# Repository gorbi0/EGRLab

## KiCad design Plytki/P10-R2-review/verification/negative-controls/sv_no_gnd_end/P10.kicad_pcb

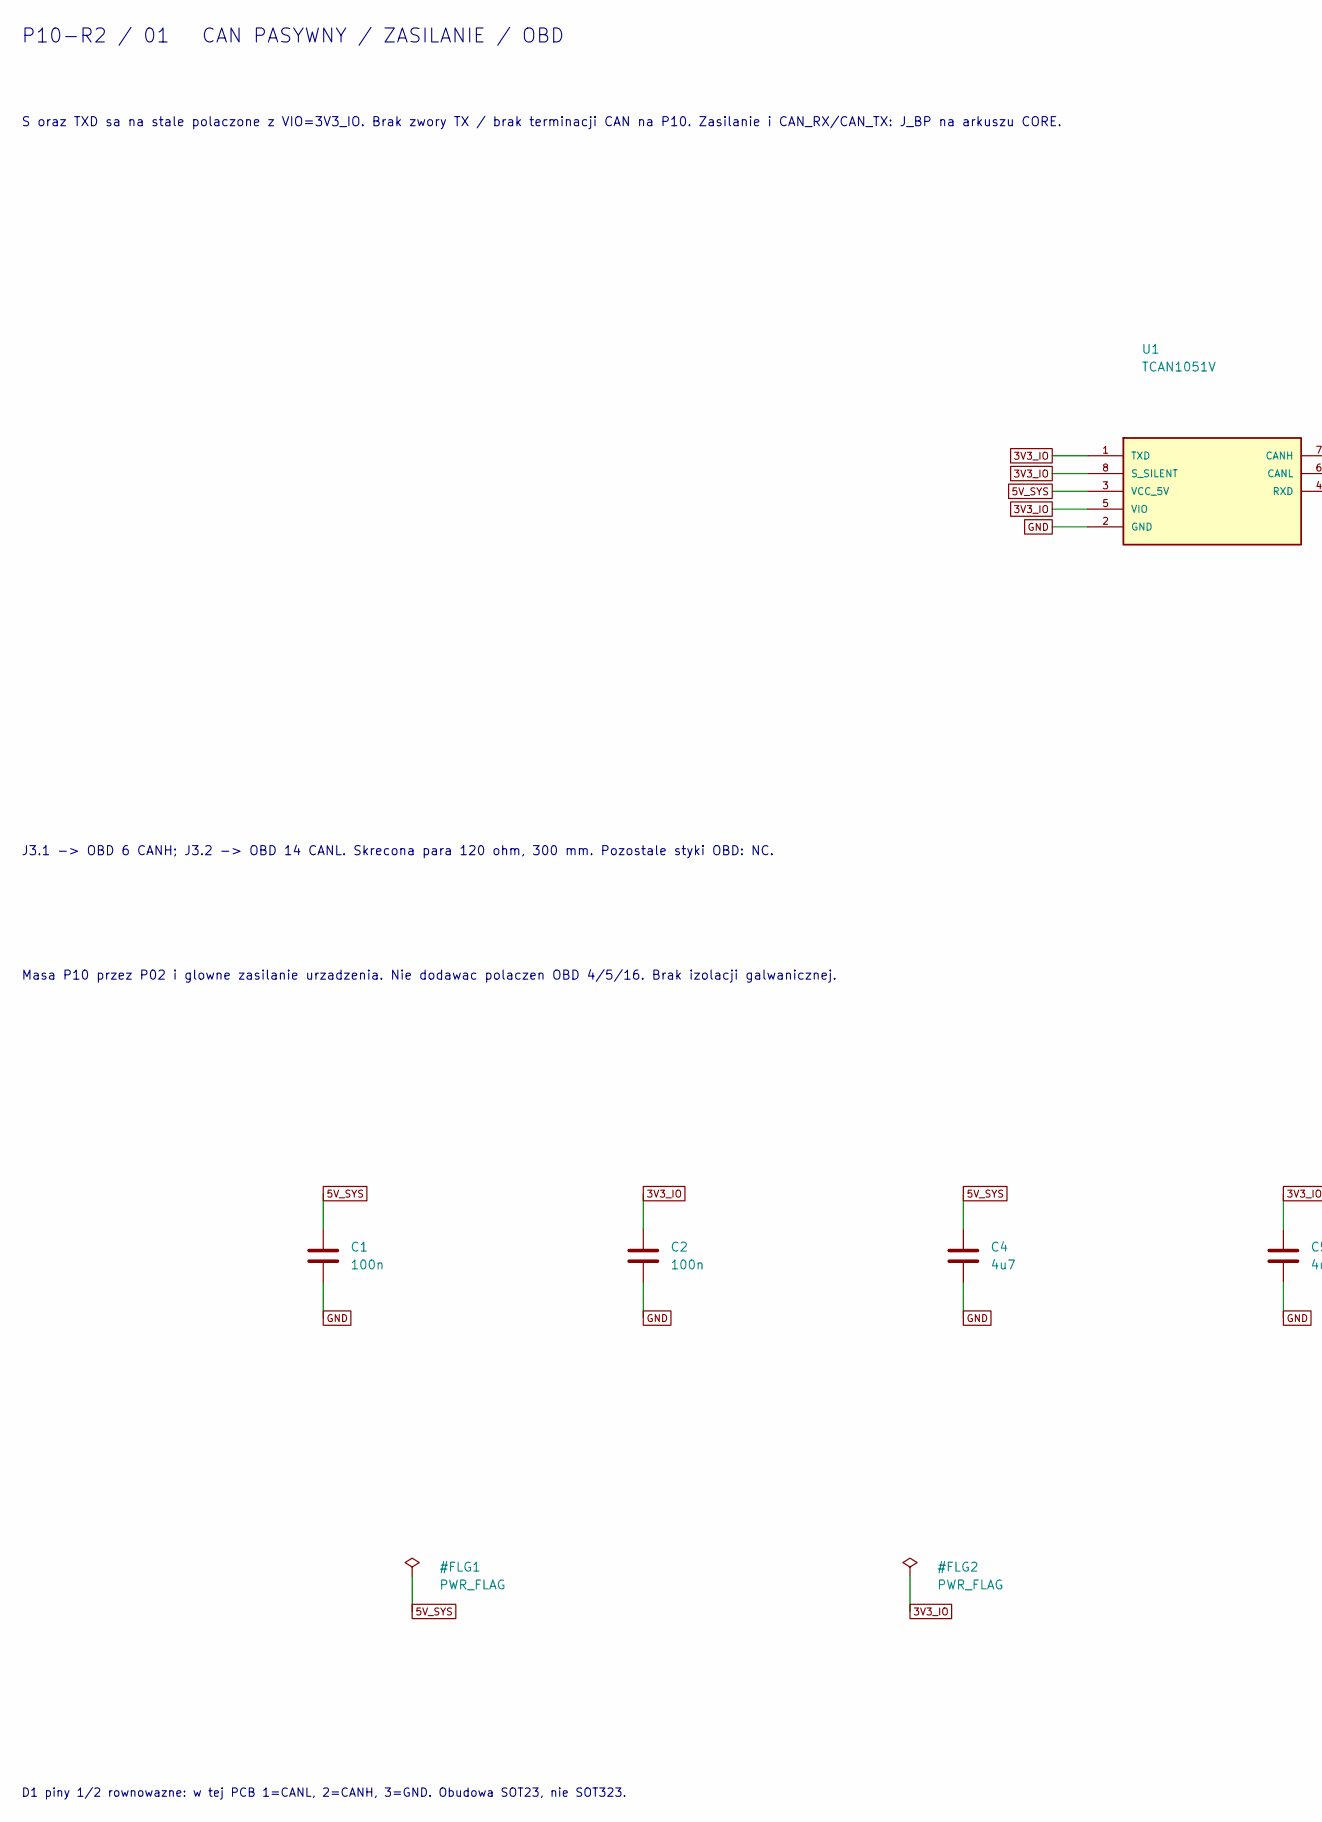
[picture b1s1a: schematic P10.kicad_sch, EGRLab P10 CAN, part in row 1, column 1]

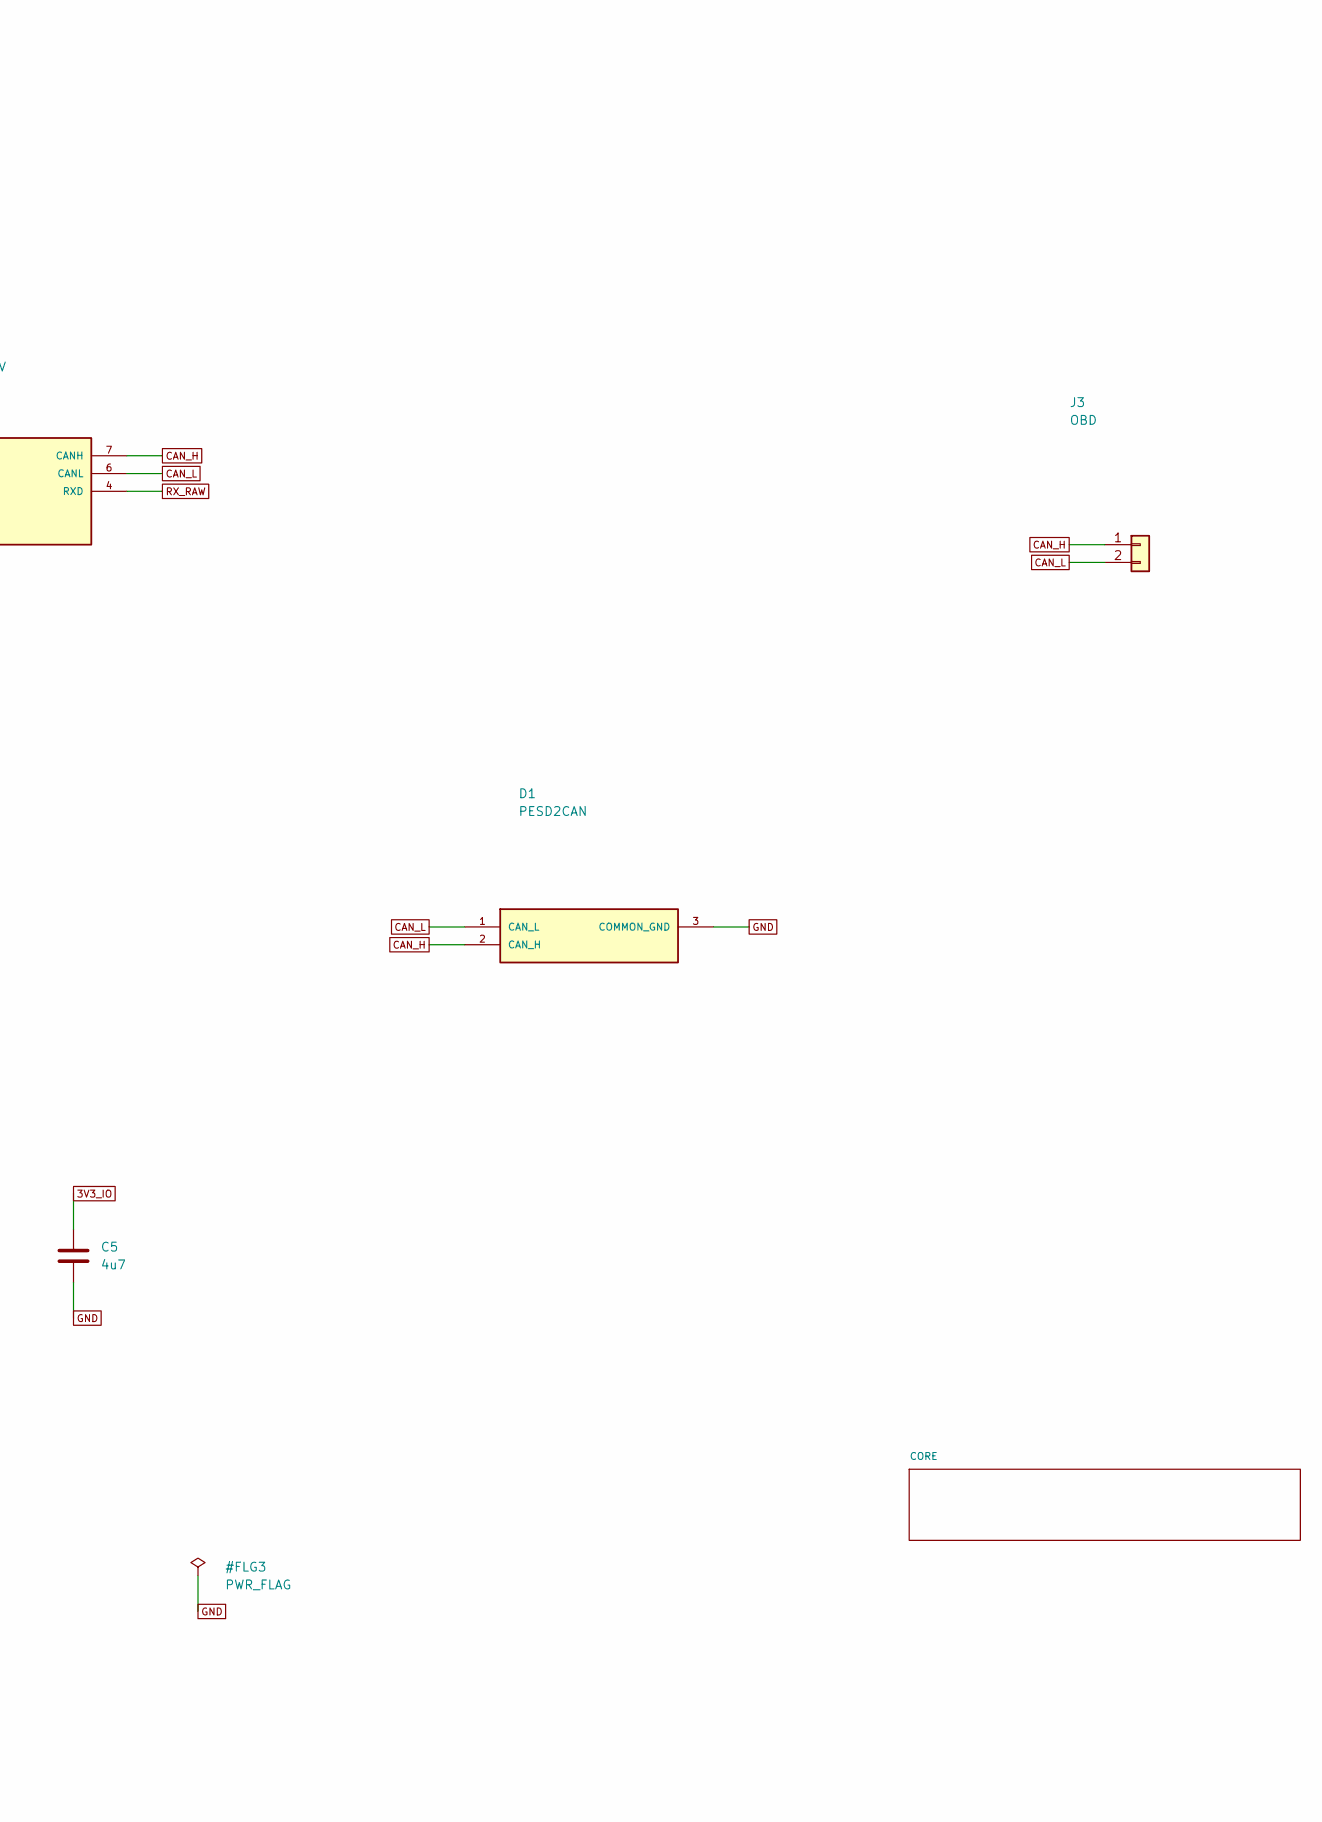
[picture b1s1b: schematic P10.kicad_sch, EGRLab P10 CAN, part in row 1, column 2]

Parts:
C1, C2: 100n; C_Disc_D5.0mm_W2.5mm_P5.00mm; MPN K104K15X7RF5TH5 Vishay 100n X7R 50V rad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
C4, C5: 4u7; C_1206_3216Metric_Pad1.33x1.80mm_HandSolder; MPN SMD 1206 X7R 25V 10% 4u7
D1: PESD2CAN; SOT-23; MPN PESD2CAN,215 Nexperia
J3: OBD; PTH_OBD; MPN Soldered 120ohm twisted pair
U1: TCAN1051V; SOIC-8_3.9x4.9mm_P1.27mm; MPN TCAN1051VDRQ1

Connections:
3V3_IO: C2.1, C5.1, U1.1 (TXD), U1.5 (VIO), U1.8 (S_SILENT); also elsewhere on the board
5V_SYS: C1.1, C4.1, U1.3 (VCC_5V); also elsewhere on the board
CAN_H: D1.2 (CAN_H), J3.1, U1.7 (CANH); also elsewhere on the board
CAN_L: D1.1 (CAN_L), J3.2, U1.6 (CANL); also elsewhere on the board
RX_RAW: U1.4 (RXD); also elsewhere on the board

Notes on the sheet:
S oraz TXD sa na stale polaczone z VIO=3V3_IO. Brak zwory TX / brak terminacji CAN na P10. Zasilanie i CAN_RX/CAN_TX: J_BP na arkuszu CORE.
J3.1 -> OBD 6 CANH; J3.2 -> OBD 14 CANL. Skrecona para 120 ohm, 300 mm. Pozostale styki OBD: NC.
Masa P10 przez P02 i glowne zasilanie urzadzenia. Nie dodawac polaczen OBD 4/5/16. Brak izolacji galwanicznej.
D1 piny 1/2 rownowazne: w tej PCB 1=CANL, 2=CANH, 3=GND. Obudowa SOT23, nie SOT323.
P10-R2 / 01 CAN PASYWNY / ZASILANIE / OBD

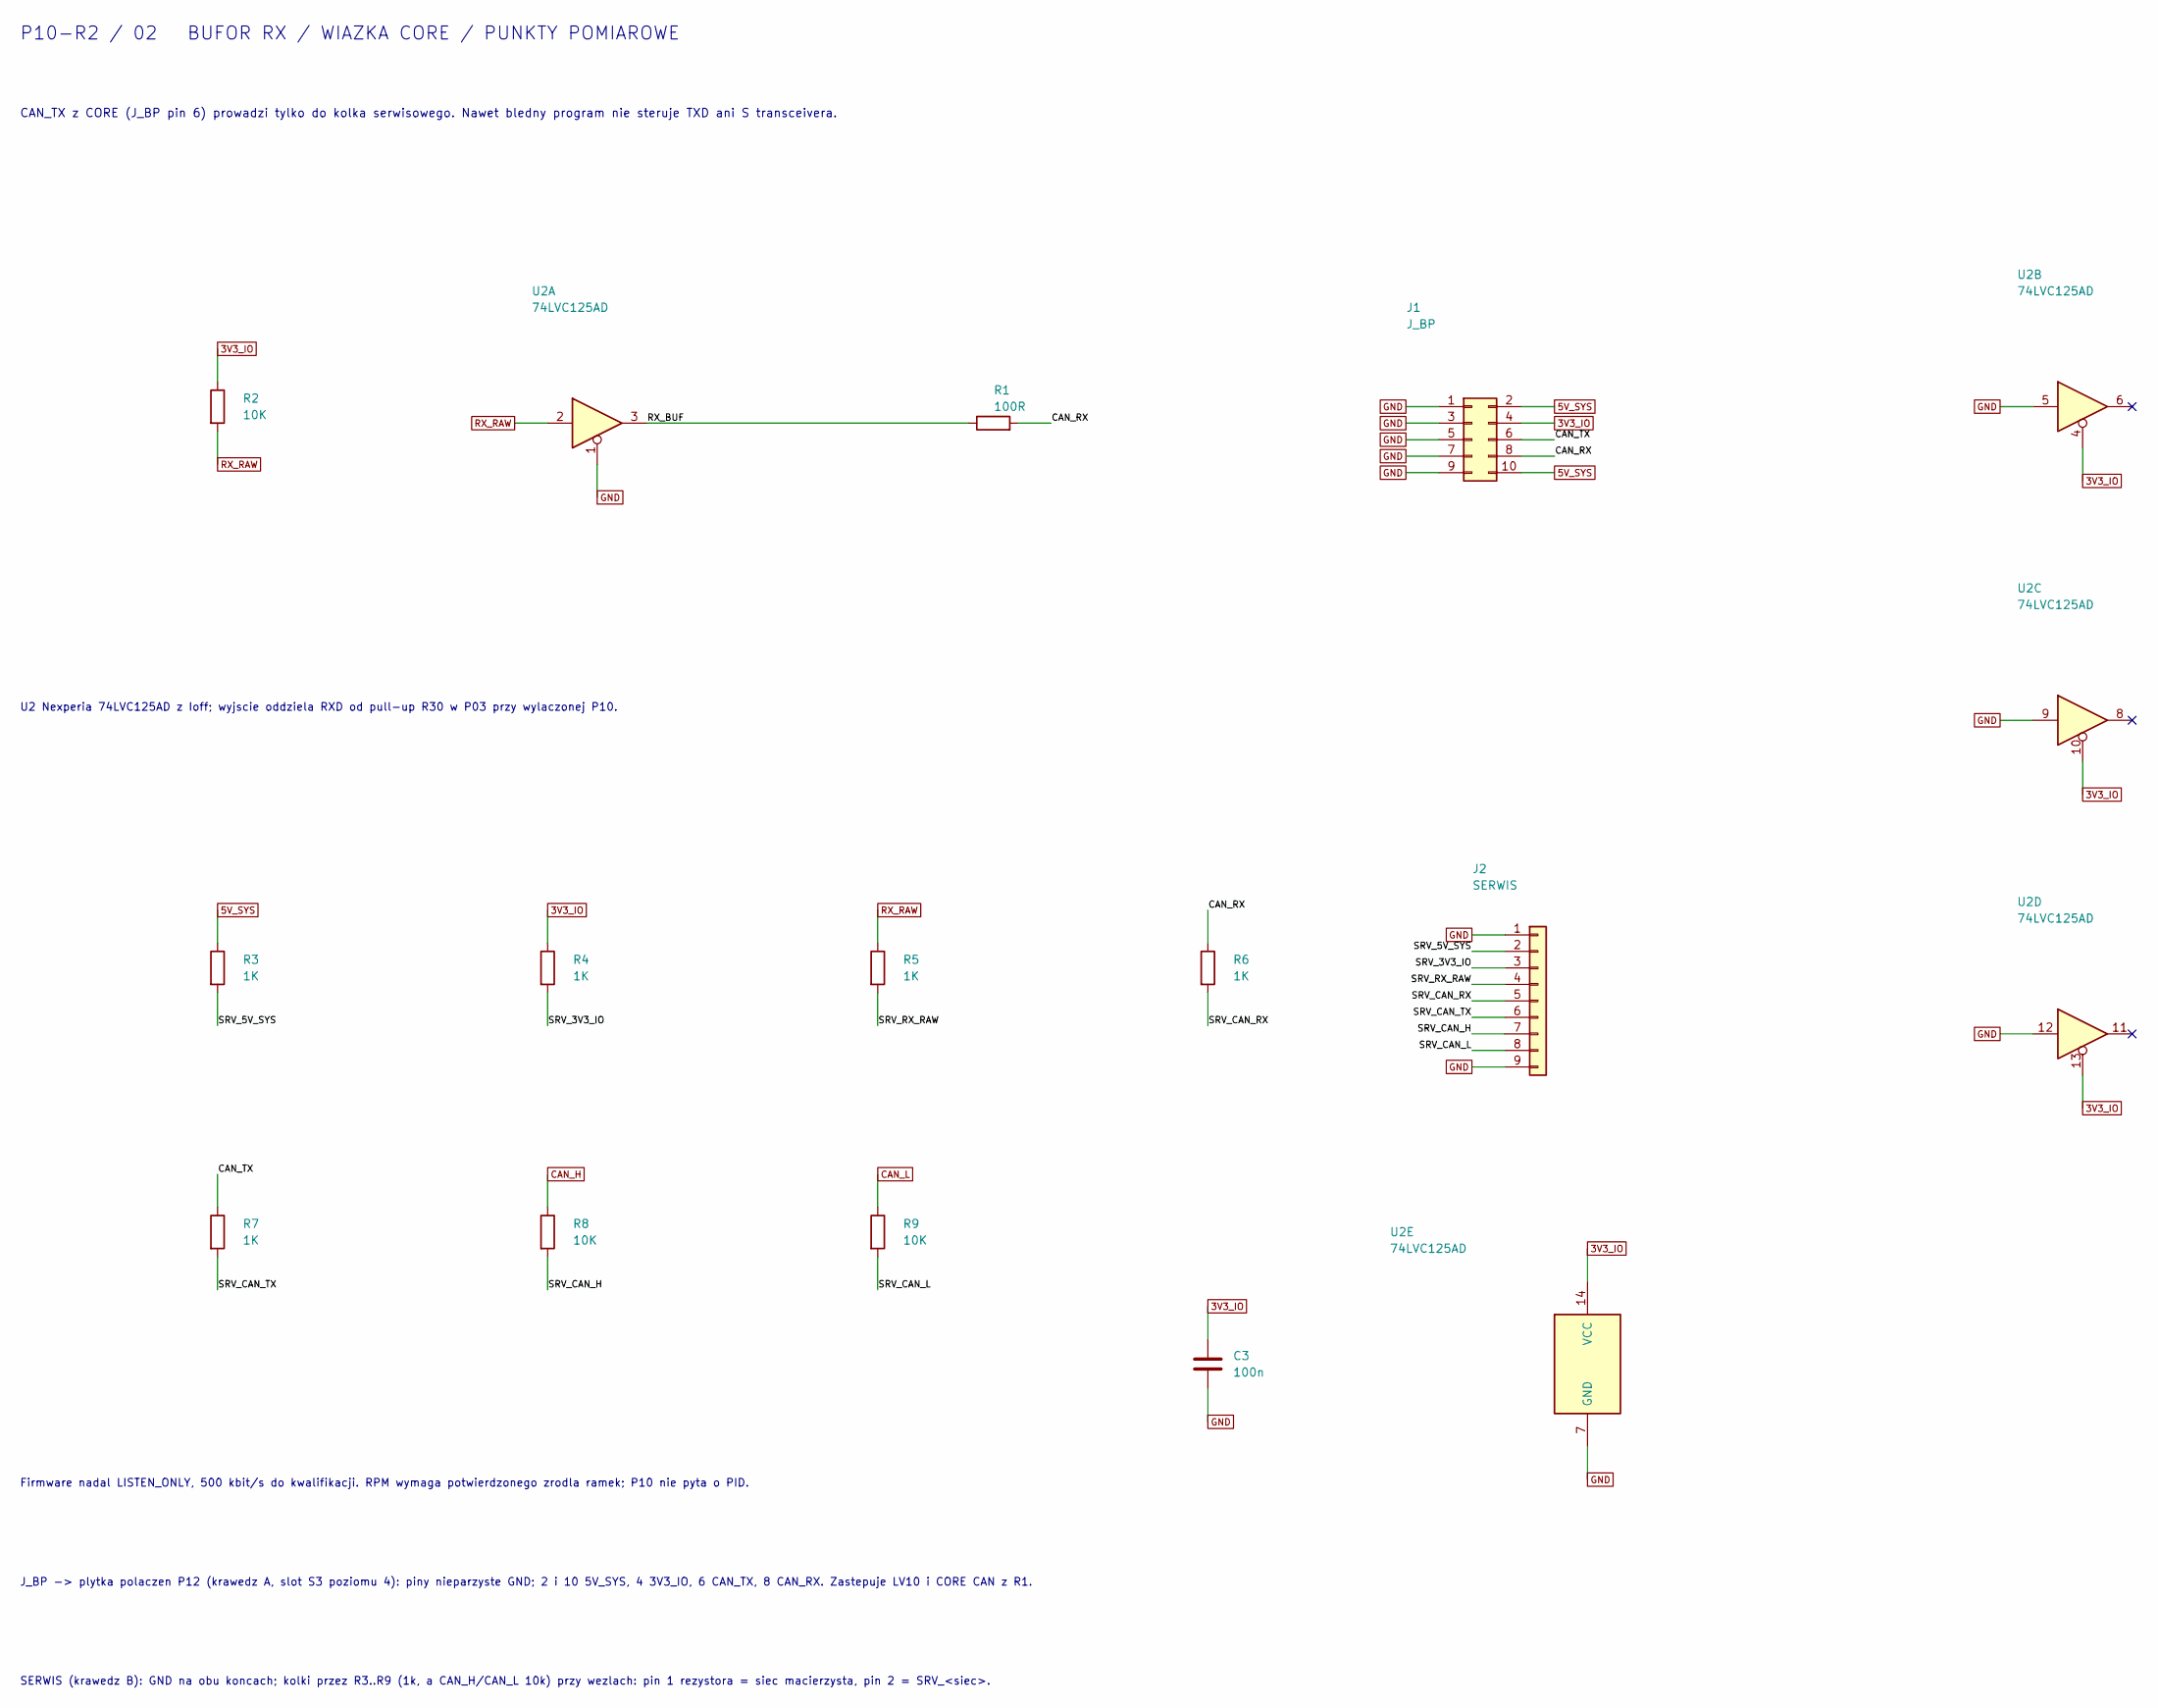
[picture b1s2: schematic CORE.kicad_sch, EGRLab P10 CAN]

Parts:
C3: 100n; C_Disc_D5.0mm_W2.5mm_P5.00mm; MPN K104K15X7RF5TH5 Vishay 100n X7R 50V rad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
J1: J_BP; IDC-Header_2x05_P2.54mm_Horizontal; MPN IDC header 2x5 2.54mm angled shrouded, 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
J2: SERWIS; PinHeader_1x09_P2.54mm_Horizontal; MPN Goldpin 1x9 2.54mm angled (buy angled s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
R1: 100R; R_1206_3216Metric_Pad1.30x1.75mm_HandSolder; MPN SMD 1206 1% 0.25W 100R
R2, R8, R9: 10K; R_Axial_DIN0207_L6.3mm_D2.5mm_P5.08mm_Vertical; MPN MF0207 Yageo 10K 1% 0.6W (owned, standi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
R3, R4, R5, R6, R7: 1K; R_1206_3216Metric_Pad1.30x1.75mm_HandSolder; MPN SMD 1206 1% 0.25W 1K
U2: 74LVC125AD; SOIC-14_3.9x8.7mm_P1.27mm; MPN 74LVC125AD,118 Nexperia

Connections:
3V3_IO: C3.1, J1.4, R2.1, R4.1, U2.4, U2.10, U2.13, U2.14 (VCC); also elsewhere on the board
5V_SYS: J1.2, J1.10, R3.1; also elsewhere on the board
/CORE/CAN_RX: J1.8, R1.2, R6.1
/CORE/CAN_TX: J1.6, R7.1
/CORE/RX_BUF: R1.1, U2.3
/CORE/SRV_3V3_IO: J2.3, R4.2
/CORE/SRV_5V_SYS: J2.2, R3.2
/CORE/SRV_CAN_H: J2.7, R8.2
/CORE/SRV_CAN_RX: J2.5, R6.2
/CORE/SRV_CAN_TX: J2.6, R7.2
/CORE/SRV_RX_RAW: J2.4, R5.2
CAN_H: R8.1; also elsewhere on the board
CAN_L: R9.1; also elsewhere on the board
RX_RAW: R2.2, R5.1, U2.2; also elsewhere on the board

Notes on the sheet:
CAN_TX z CORE (J_BP pin 6) prowadzi tylko do kolka serwisowego. Nawet bledny program nie steruje TXD ani S transceivera.
U2 Nexperia 74LVC125AD z Ioff; wyjscie oddziela RXD od pull-up R30 w P03 przy wylaczonej P10.
J_BP -> plytka polaczen P12 (krawedz A, slot S3 poziomu 4): piny nieparzyste GND; 2 i 10 5V_SYS, 4 3V3_IO, 6 CAN_TX, 8 CAN_RX. Zastepuje LV10 i CORE CAN z R1.
SERWIS (krawedz B): GND na obu koncach; kolki przez R3..R9 (1k, a CAN_H/CAN_L 10k) przy wezlach: pin 1 rezystora = siec macierzysta, pin 2 = SRV_<siec>.
Firmware nadal LISTEN_ONLY, 500 kbit/s do kwalifikacji. RPM wymaga potwierdzonego zrodla ramek; P10 nie pyta o PID.
P10-R2 / 02 BUFOR RX / WIAZKA CORE / PUNKTY POMIAROWE

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
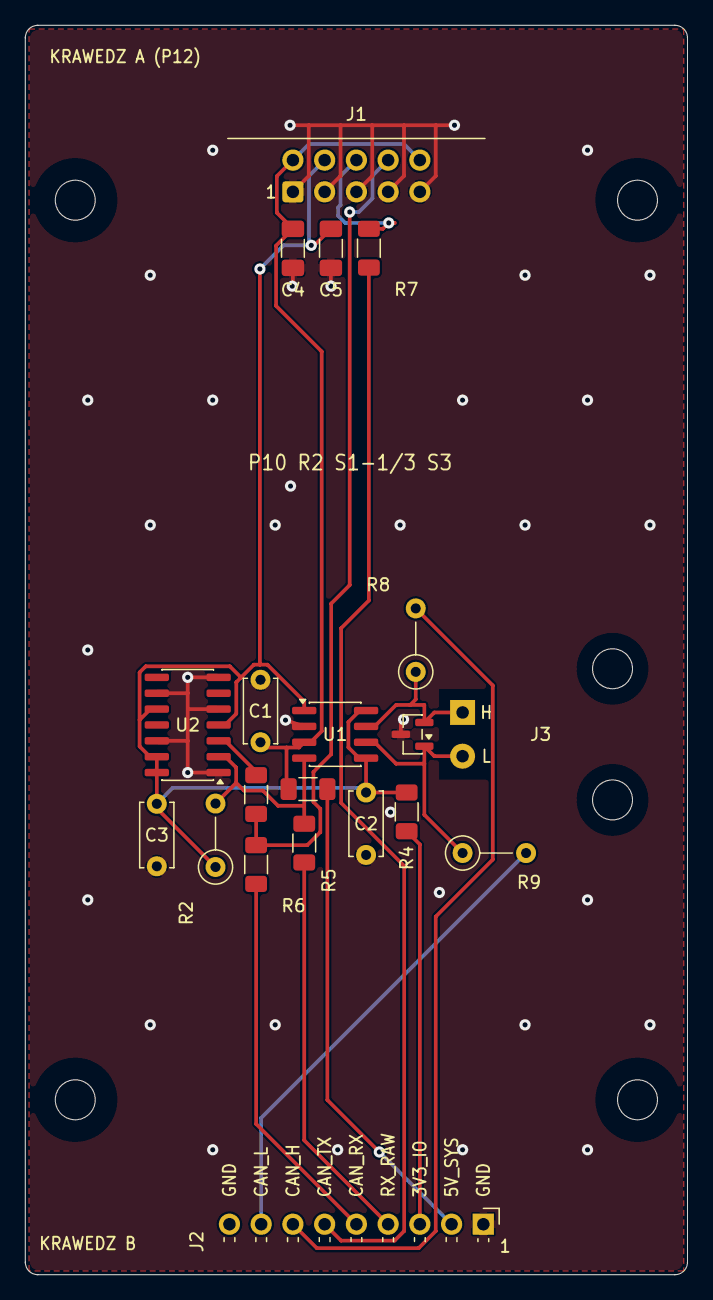
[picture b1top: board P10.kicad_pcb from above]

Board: 2 copper layers, 53.0 x 100.0 mm, 24 parts (0 on the bottom side), 16 nets.

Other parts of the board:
H1, H2, H3, H4: M3 NPTH

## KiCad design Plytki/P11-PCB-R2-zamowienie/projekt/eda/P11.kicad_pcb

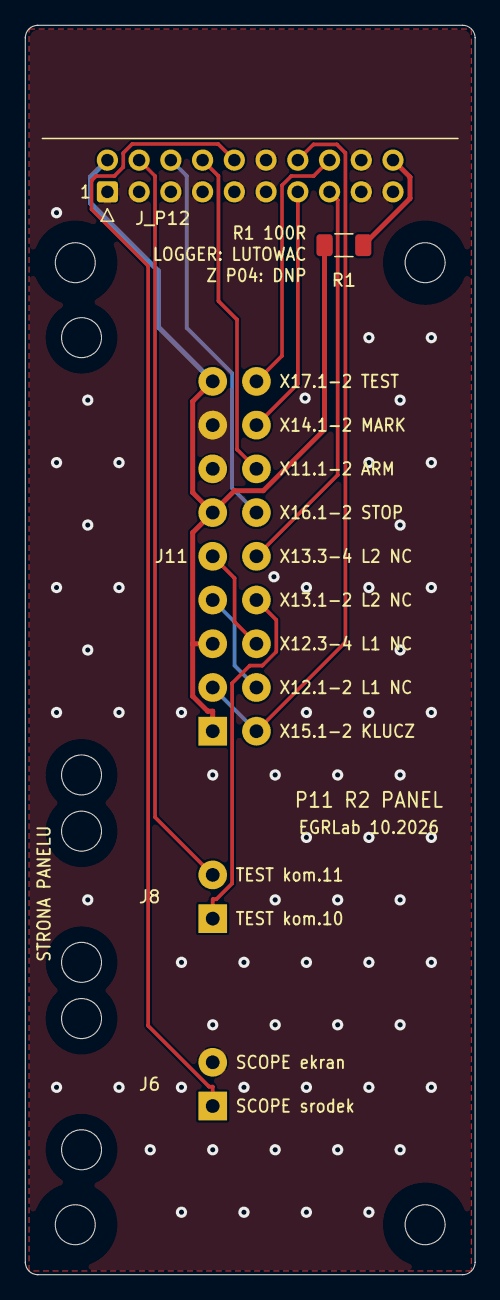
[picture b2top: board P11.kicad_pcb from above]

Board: 2 copper layers, 36.0 x 100.0 mm, 9 parts (0 on the bottom side), 14 nets.

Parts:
H1, H2, H3, H4: M3 NPTH
J6: SCOPE tail; FIELD_PAIR2
J8: TEST signal; FIELD_PAIR2
J11: CONTACTS; FIELD_CONTACT18
J_P12: IDC 2x10 katowe do P12; IDC-Header_2x10_P2.54mm_Horizontal
R1: 100R; R_1206_3216Metric_Pad1.30x1.75mm_HandSolder

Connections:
/3V3_IO: J_P12.20, R1.1
/CONTACTS/DIAG_L1_L2: J11.6, J11.9
/CONTACTS/ILK_L1_L2: J11.4, J11.7
/CONTACTS/LOOP_OUT: J8.1, J11.8
/N_J_SCOPE_HOT: J6.1, J_P12.10
ARM_CONTACT: J11.14, J_P12.8
GND: J6.2, J11.13, J11.15, J_P12.1, J_P12.3, J_P12.5, J_P12.7, J_P12.9, J_P12.11, J_P12.12, J_P12.17, J_P12.18, J_P12.19
LOGGER_CLEAR: J11.10, J_P12.15
MARK: J11.16, J_P12.13
MECH_OK: J8.2, J_P12.4
PANEL_3V3: J11.1, J11.5, J11.11, J11.17, J_P12.2, R1.2
STOP_NC_OUT: J11.12, J_P12.6
TEST_KEY: J11.2, J11.3, J_P12.14
TEST_PRESENT: J11.18, J_P12.16
